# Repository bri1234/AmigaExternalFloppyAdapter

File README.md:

# AmigaExternalFloppyAdapter

KiCAD Project based on:

https://github.com/retronicdesign/AmigaExternalFloppyAdapter

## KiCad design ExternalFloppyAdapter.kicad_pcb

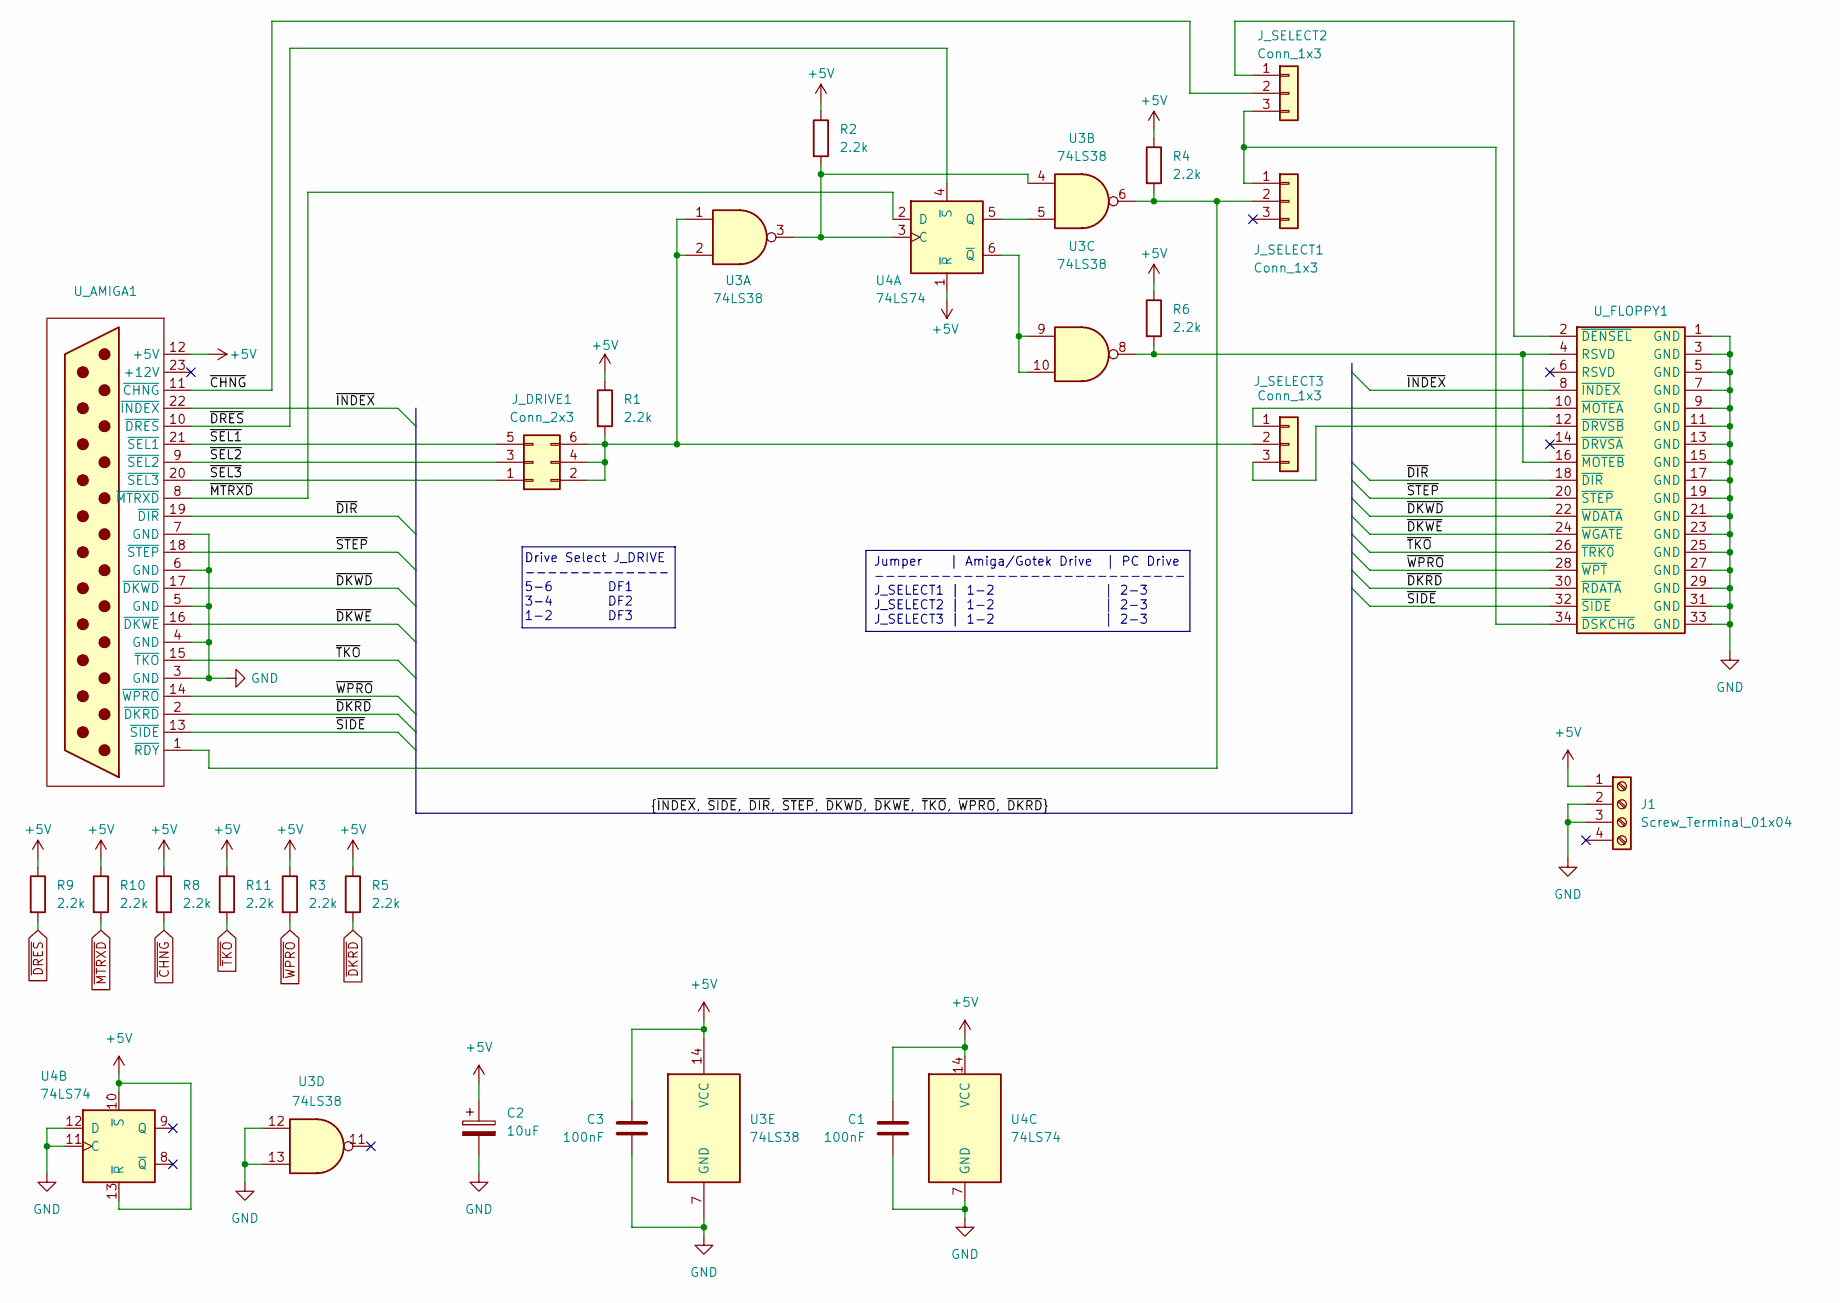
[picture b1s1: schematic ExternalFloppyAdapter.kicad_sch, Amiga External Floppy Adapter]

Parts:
C1, C3: 100nF; C_Rect_L4.6mm_W3.0mm_P2.50mm_MKS02_FKP02
C2: 10uF; CP_Radial_D8.0mm_P3.50mm
J1: Screw_Terminal_01x04; Molex_KK-254_AE-6410-04A_1x04_P2.54mm_Vertical
J_DRIVE1: Conn_2x3; PinHeader_2x03_P2.54mm_Vertical
J_SELECT1, J_SELECT2, J_SELECT3: Conn_1x3; PinHeader_1x03_P2.54mm_Vertical
R1, R2, R3, R4, R5, R6, R8, R9, R10, R11: 2.2k; R_Axial_DIN0309_L9.0mm_D3.2mm_P12.70mm_Horizontal
U3: 74LS38; DIP-14_W7.62mm_LongPads
U4: 74LS74; DIP-14_W7.62mm_LongPads
U_AMIGA1: ExternalFloppyConnectorEdgeMount
U_FLOPPY1: PinSocket_2x17_P2.54mm_Vertical

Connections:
+5V: C1.1, C2.1, C3.1, J1.1, R1.1, R2.1, R3.1, R4.1, R5.1, R6.1, R8.1, R9.1, R10.1, R11.1, U3.14 (VCC), U4.1 (~R), U4.10 (~S), U4.13 (~R), U4.14 (VCC), U_AMIGA1.12 (+5V)
/~DIR: U_AMIGA1.19 (~DIR), U_FLOPPY1.18 (~DIR)
/~DKWD: U_AMIGA1.17 (~DKWD), U_FLOPPY1.22 (~WDATA)
/~DKWE: U_AMIGA1.16 (~DKWE), U_FLOPPY1.24 (~WGATE)
/~INDEX: U_AMIGA1.22 (~INDEX), U_FLOPPY1.8 (~INDEX)
/~SEL1: J_DRIVE1.5, U_AMIGA1.21 (~SEL1)
/~SEL2: J_DRIVE1.3, U_AMIGA1.9 (~SEL2)
/~SEL3: J_DRIVE1.1, U_AMIGA1.20 (~SEL3)
/~SIDE: U_AMIGA1.13 (~SIDE), U_FLOPPY1.32 (~SIDE)
/~STEP: U_AMIGA1.18 (~STEP), U_FLOPPY1.20 (~STEP)
GND: C1.2, C2.2, C3.2, J1.2, J1.3, U3.7 (GND), U3.12, U3.13, U4.7 (GND), U4.11 (C), U4.12 (D), U_AMIGA1.3 (GND), U_AMIGA1.4 (GND), U_AMIGA1.5 (GND), U_AMIGA1.6 (GND), U_AMIGA1.7 (GND), U_FLOPPY1.1 (GND), U_FLOPPY1.3 (GND), U_FLOPPY1.5 (GND), U_FLOPPY1.7 (GND), U_FLOPPY1.9 (GND), U_FLOPPY1.11 (GND), U_FLOPPY1.13 (GND), U_FLOPPY1.15 (GND), U_FLOPPY1.17 (GND), U_FLOPPY1.19 (GND), U_FLOPPY1.21 (GND), U_FLOPPY1.23 (GND), U_FLOPPY1.25 (GND), U_FLOPPY1.27 (GND), U_FLOPPY1.29 (GND), U_FLOPPY1.31 (GND), U_FLOPPY1.33 (GND)
unnamed: J_DRIVE1.2, J_DRIVE1.4, J_DRIVE1.6, J_SELECT3.2, R1.2, U3.1, U3.2
unnamed: J_SELECT1.1, J_SELECT2.3, U_FLOPPY1.34 (~DSKCHG)
unnamed: J_SELECT1.2, R4.2, U3.6, U_AMIGA1.1 (~RDY)
unnamed: J_SELECT2.1, U_FLOPPY1.2 (~DENSEL)
unnamed: J_SELECT3.1, U_FLOPPY1.10 (~MOTEA)
unnamed: J_SELECT3.3, U_FLOPPY1.12 (~DRVSB)
unnamed: R2.2, U3.3, U3.4, U4.3 (C)
unnamed: U3.5, U4.5 (Q)
unnamed: U3.9, U3.10, U4.6 (~Q)
unnamed: R6.2, U3.8, U_FLOPPY1.4 (RSVD), U_FLOPPY1.16 (~MOTEB)
~CHNG: J_SELECT2.2, R8.2, U_AMIGA1.11 (~CHNG)
~DKRD: R5.2, U_AMIGA1.2 (~DKRD), U_FLOPPY1.30 (~RDATA)
~DRES: R9.2, U4.4 (~S), U_AMIGA1.10 (~DRES)
~MTRXD: R10.2, U4.2 (D), U_AMIGA1.8 (~MTRXD)
~TKO: R11.2, U_AMIGA1.15 (~TKO), U_FLOPPY1.26 (~TRK0)
~WPRO: R3.2, U_AMIGA1.14 (~WPRO), U_FLOPPY1.28 (~WPT)

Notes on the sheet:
Drive Select J_DRIVE ------------- 5-6 DF1 3-4 DF2 1-2 DF3
Jumper | Amiga/Gotek Drive | PC Drive ---------------------------- J_SELECT1 | 1-2 | 2-3 J_SELECT2 | 1-2 | 2-3 J_SELECT3 | 1-2 | 2-3

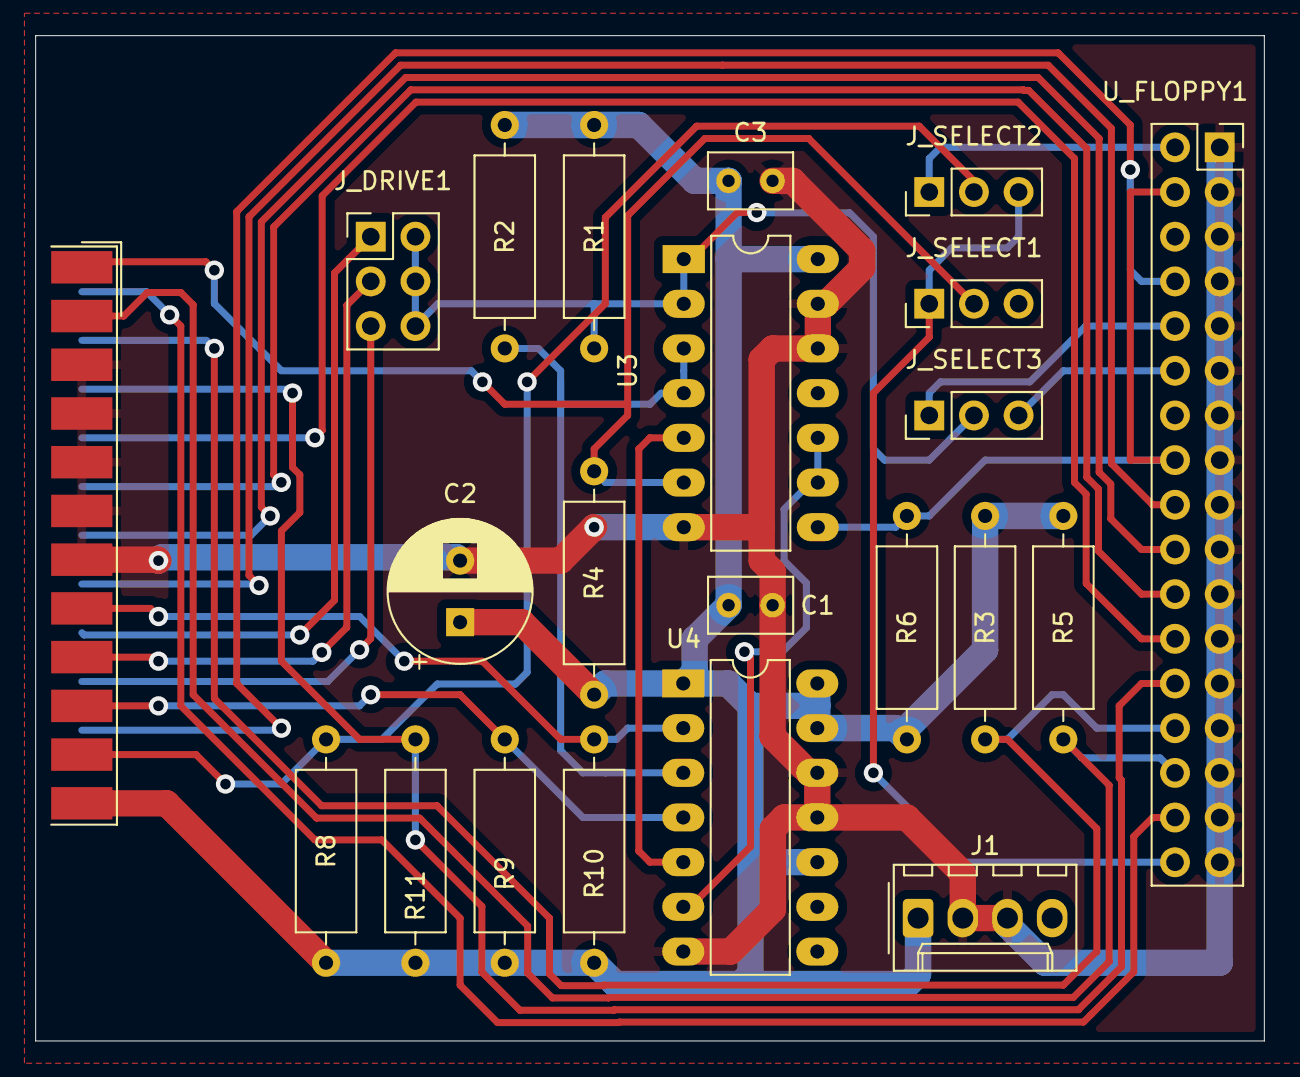
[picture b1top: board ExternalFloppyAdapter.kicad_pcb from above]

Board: 2 copper layers, 69.8 x 57.2 mm, 22 parts (0 on the bottom side), 27 nets.

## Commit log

2025-01-31 initial checkin
2025-01-31 PDF added
2025-02-01 Layout reworked
2025-02-01 Floppy connector changed, layout improved
